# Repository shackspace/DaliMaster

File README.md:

DaliMaster
==========

A Dali master communication interface using custom circuit and openwrt on TP-Link MR-3020

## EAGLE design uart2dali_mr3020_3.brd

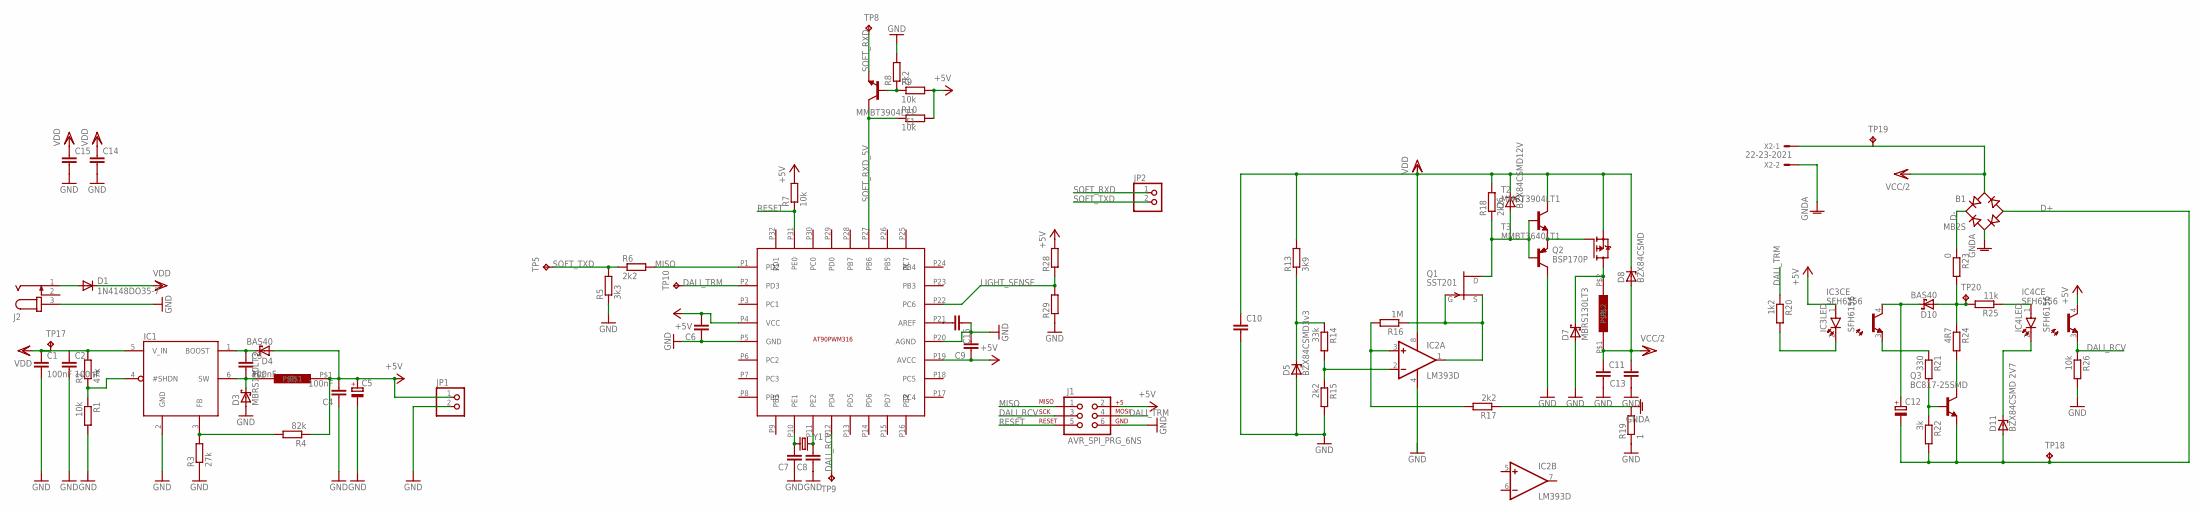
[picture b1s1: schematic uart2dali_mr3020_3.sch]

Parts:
B1: MB2S; SOIC-4
C1, C2, C3, C4: 100nF; C0805
C5: CPOL-EUCT7343; CT7343
C6, C7, C8, C9, C10, C16: C-EUC0603; C0603
C11, C13, C14, C15: C-EUC0805; C0805
C12: CPOL-EUCT6032; CT6032
D1: 1N4148DO35-7; DO35-7
D3, D7: MBRS130LT3; SMB
D4, D10: BAS40; SOT23
D5: BZX84CSMD3v3; TO236
D6: BZX84CSMD12V; TO236
D8: BZX84CSMD; TO236
D11: BZX84CSMD 2V7; TO236
IC1: LT1933ES6; SOT23-6
IC2: LM393D; SO08
IC3, IC4: SFH6156; SFH
J1: AVR_SPI_PRG_6NS; 2X3-NS
J2: JACK-PLUG1; SPC4078
JP1, JP2: PINHD-1X2; 1X02
Q1: SST201; SOT23
Q2: BSP170P; SOT223
Q3: BC817-25SMD; SOT23-BEC
R1, R7, R9, R10, R26: 10k; R0603
R2: 47k; R0603
R3: 27k; R0603
R4: 82k; R0603
R5: 3k3; R0603
R6, R8, R15, R17, R18: 2k2; R0603
R13: 3k9; R0603
R14: 33k; R0603
R16: 1M; R0603
R19: 1; R0603
R20: 1k2; R0603
R21: 330; R0603
R22: 3k; R0603
R23: 0; R0603
R24: 4R7; R0603
R25: 11k; R0603
R28: R-EU_0207/2V; 0207/2V
R29: R-EU_R0603; R0603
T1, T2: MMBT3904LT1; SOT23-BEC
T3: MMBT3640LT1; SOT23-BEC
TP5, TP8, TP9, TP10, TP17, TP18, TP19, TP20: TPB1,27; B1,27
U$1: KMP_2330_UNSHIELDED 33uH; KMP_2330_UNSHIELDED
U$2: AT90PWM316; QFN32_7MM
U$3: SDR0805
X2: 22-23-2021
Y1: CRYSTALTXC-7A; CRYSTAL-TXC-7A

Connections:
+5V: C4.2, C5.+, C6.2, C9.1, D4.1 (A), IC3.1 (A), IC4.4 (C), J1.2, JP1.1, R4.1, R7.2, R9.2, R10.2, R28.2, U$1.P$1, U$2.P4 (VCC), U$2.P19 (AVCC)
D+: B1.-, C12.-, D11.A, Q3.E, R22.2, TP18.TP
D-: B1.+, R23.1
DALI_RCV: J1.3, TP9.TP, U$2.P12 (PD4)
DALI_TRM: J1.4, R20.1, TP10.TP, U$2.P2 (PD3)
GND: C1.2, C2.2, C4.1, C5.-, C6.1, C7.1, C8.1, C9.2, C10.2, C11.2, C13.1, C14.2, C15.2, C16.1, D3.A, D5.A, D7.A, IC1.2 (GND), IC2.4 (V-), J1.6, J2.3, JP1.2, R1.2, R3.1, R5.1, R8.2, R15.2, R19.1, R26.2, R29.1, T3.C, U$2.P5 (GND), U$2.P20 (AGND)
GNDA: B1.~2 (AC2), R17.1, R19.2, X2.2
LIGHT_SENSE: R28.1, R29.2, U$2.P22 (PC6)
MISO: J1.1, R6.2, U$2.P1 (PD2)
unnamed: IC3.2 (K), R20.2
unnamed: IC2.2 (-IN), R14.2, R15.1
unnamed: IC1.4 (#SHDN), R1.1, R2.1
unnamed: C12.+, D10.3 (C), IC3.4 (C)
unnamed: IC3.3 (E), R21.1
unnamed: Q3.B, R21.2, R22.1
unnamed: IC4.3 (E), R26.1
unnamed: C16.2, U$2.P21 (AREF)
unnamed: D10.1 (A), R23.2, R24.1, R25.2, TP20.TP
unnamed: Q3.C, R24.2
unnamed: IC4.1 (A), R25.1
unnamed: D11.C, IC4.2 (K)
unnamed: C7.2, U$2.P10 (PE1), Y1.P$1 (1)
unnamed: C8.2, U$2.P11 (PE2), Y1.P$2 (2)
unnamed: R8.1, R9.1, T1.B
unnamed: IC2.1 (OUT), Q1.2 (S), Q1.3 (G), R16.1
unnamed: D1.A, J2.1
unnamed: C3.1, D4.3 (C), IC1.1 (BOOST)
unnamed: C3.2, D3.C, IC1.6 (SW), U$1.P$2
unnamed: D7.C, Q2.2 (D), Q2.4 (D), U$3.P$2
unnamed: IC1.3 (FB), R3.2, R4.2
unnamed: Q2.1 (G), T2.E, T3.E
unnamed: D6.A, Q1.1 (D), R18.1, T2.B, T3.B
unnamed: D5.C, R13.1, R14.1
unnamed: IC2.3 (+IN), R16.2, R17.2
RESET: J1.5, R7.1, U$2.P31 (PE0)
SOFT_RXD: JP2.1, T1.E, TP8.TP
SOFT_RXD_5V: R10.1, T1.C, U$2.P27 (PB6)
SOFT_TXD: JP2.2, R5.2, R6.1, TP5.TP
VCC/2: B1.~1 (AC1), C11.1, C13.2, D8.A, TP19.TP, U$3.P$1, X2.1
VDD: C1.1, C2.1, C10.1, C14.1, C15.1, D1.C, D6.C, D8.C, IC1.5 (V_IN), IC2.8 (V+), Q2.3 (S), R2.2, R13.2, R18.2, T2.C, TP17.TP

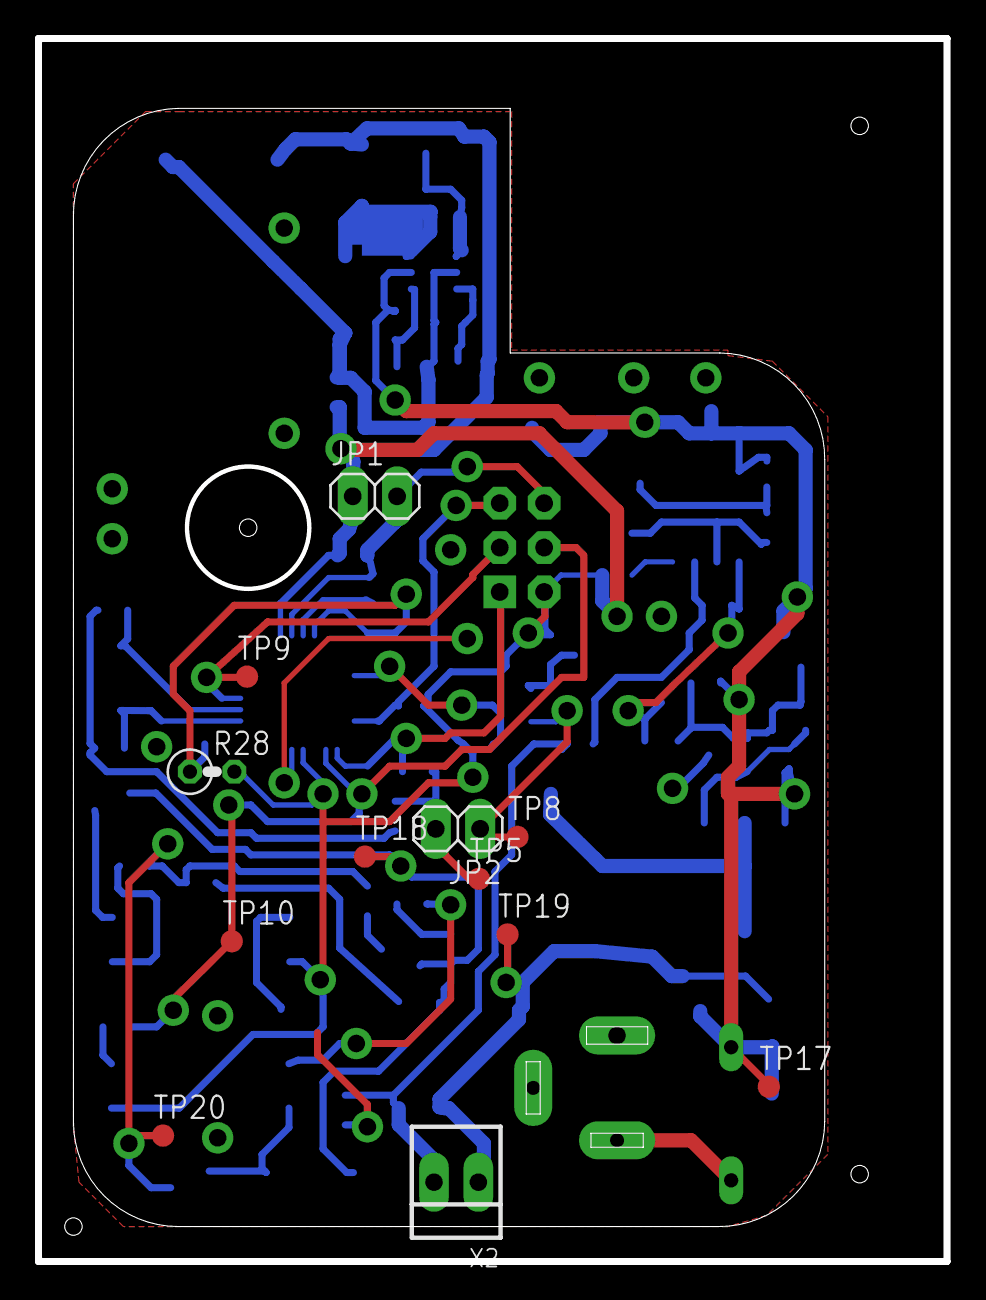
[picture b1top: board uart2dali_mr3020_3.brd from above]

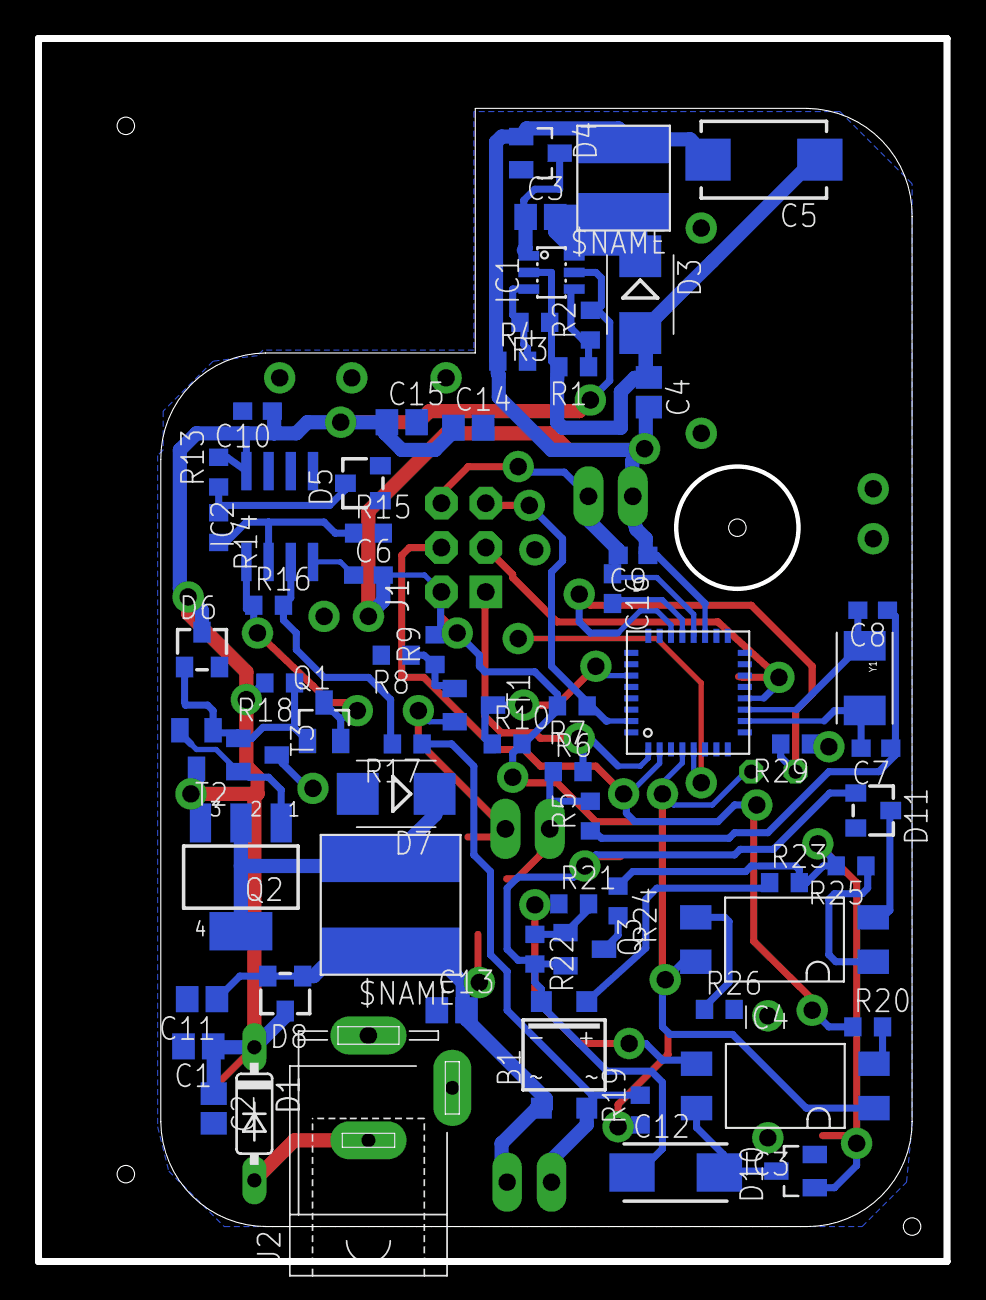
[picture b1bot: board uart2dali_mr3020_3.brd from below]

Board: 2 copper layers, 52.0 x 70.0 mm, 79 parts (67 on the bottom side), 40 nets.

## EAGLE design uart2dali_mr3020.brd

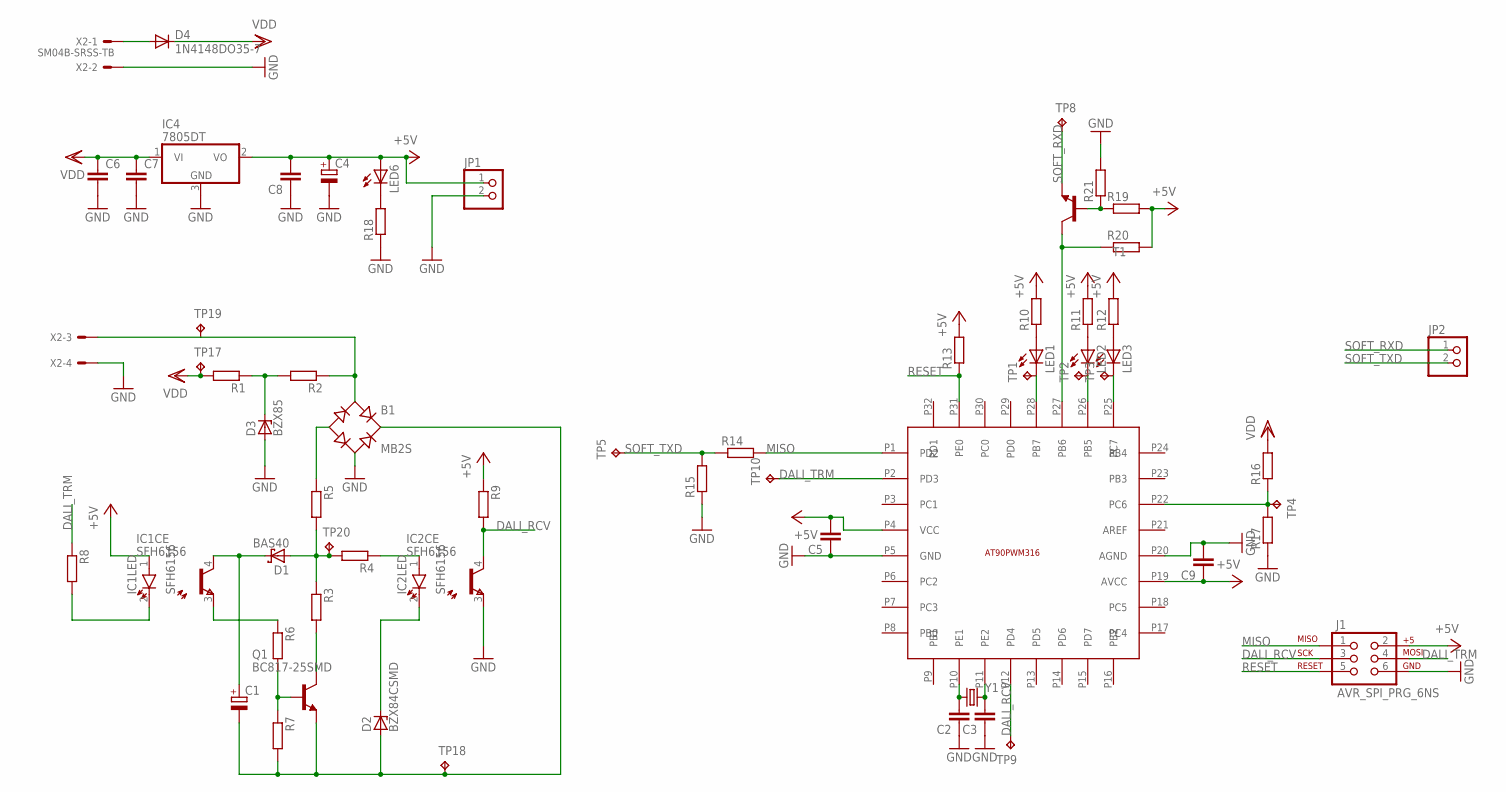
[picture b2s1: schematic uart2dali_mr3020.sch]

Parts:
B1: MB2S; SOIC-4
C1: CPOL-EUCT6032; CT6032
C2, C3, C5, C9: C-EUC0603; C0603
C4: CPOL-EUCT7343; CT7343
C6, C7, C8: C-EUC0805; C0805
D1: BAS40; SOT23
D2: BZX84CSMD; TO236
D3: BZX85; DO41Z10
D4: 1N4148DO35-7; DO35-7
IC1, IC2: SFH6156; SFH
IC4: 7805DT; TO252
J1: AVR_SPI_PRG_6NS; 2X3-NS
JP1, JP2: PINHD-1X2; 1X02
LED1, LED2, LED3, LED6: LEDCHIPLED_0805; CHIPLED_0805
Q1: BC817-25SMD; SOT23-BEC
R1, R2: R-EU_0204/7; 0204/7
R3, R4, R5, R6, R7, R8, R9, R10, R11, R12, R13, R14, R15, R16, R17, R18, R19, R20, R21: R-EU_R0603; R0603
T1: -NPN-SOT23-EBC; SOT23-EBC
TP1, TP2, TP3, TP4, TP5, TP8, TP9, TP10, TP17, TP18, TP19, TP20: TPB1,27; B1,27
U$1: AT90PWM316; QFN32_7MM
X2: SM04B-SRSS-TB
Y1: CRYSTALTXC-7A; CRYSTAL-TXC-7A

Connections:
+5V: C4.+, C5.2, C8.2, C9.1, IC1.1 (A), IC4.2 (VO), J1.2, JP1.1, LED6.A, R9.1, R10.2, R11.2, R12.2, R13.2, R19.2, R20.2, U$1.P4 (VCC), U$1.P19 (AVCC)
DALI_RCV: IC2.4 (C), J1.3, R9.2, TP9.TP, U$1.P12 (PD4)
DALI_TRM: J1.4, R8.1, TP10.TP, U$1.P2 (PD3)
GND: B1.~2 (AC2), C2.1, C3.1, C4.-, C5.1, C6.2, C7.2, C8.1, C9.2, D3.A, IC2.3 (E), IC4.3 (GND), J1.6, JP1.2, R15.1, R17.1, R18.1, R21.2, U$1.P5 (GND), U$1.P20 (AGND), X2.2, X2.4
MISO: J1.1, R14.2, U$1.P1 (PD2)
unnamed: IC1.2 (K), R8.2
unnamed: B1.~1 (AC1), R2.1, TP19.TP, X2.3
unnamed: D3.C, R1.1, R2.2
unnamed: C1.+, D1.3 (C), IC1.4 (C)
unnamed: IC1.3 (E), R6.1
unnamed: Q1.B, R6.2, R7.1
unnamed: B1.+, C1.-, D2.A, Q1.E, R7.2, TP18.TP
unnamed: LED1.A, R10.1
unnamed: D1.1 (A), R3.1, R4.2, R5.2, TP20.TP
unnamed: Q1.C, R3.2
unnamed: IC2.1 (A), R4.1
unnamed: D2.C, IC2.2 (K)
unnamed: B1.-, R5.1
unnamed: LED2.A, R11.1
unnamed: LED3.A, R12.1
unnamed: C2.2, U$1.P10 (PE1), Y1.P$1 (1)
unnamed: C3.2, U$1.P11 (PE2), Y1.P$2 (2)
unnamed: R19.1, R21.1, T1.B
unnamed: R20.1, T1.C, U$1.P27 (PB6)
unnamed: D4.A, X2.1
unnamed: LED3.C, TP3.TP, U$1.P25 (PC7)
unnamed: LED2.C, TP2.TP, U$1.P26 (PB5)
unnamed: LED1.C, TP1.TP, U$1.P28 (PB7)
unnamed: R16.1, R17.2, TP4.TP, U$1.P22 (PC6)
unnamed: LED6.C, R18.2
RESET: J1.5, R13.1, U$1.P31 (PE0)
SOFT_RXD: JP2.1, T1.E, TP8.TP
SOFT_TXD: JP2.2, R14.1, R15.2, TP5.TP
VDD: C6.1, C7.1, D4.C, IC4.1 (VI), R1.2, R16.2, TP17.TP

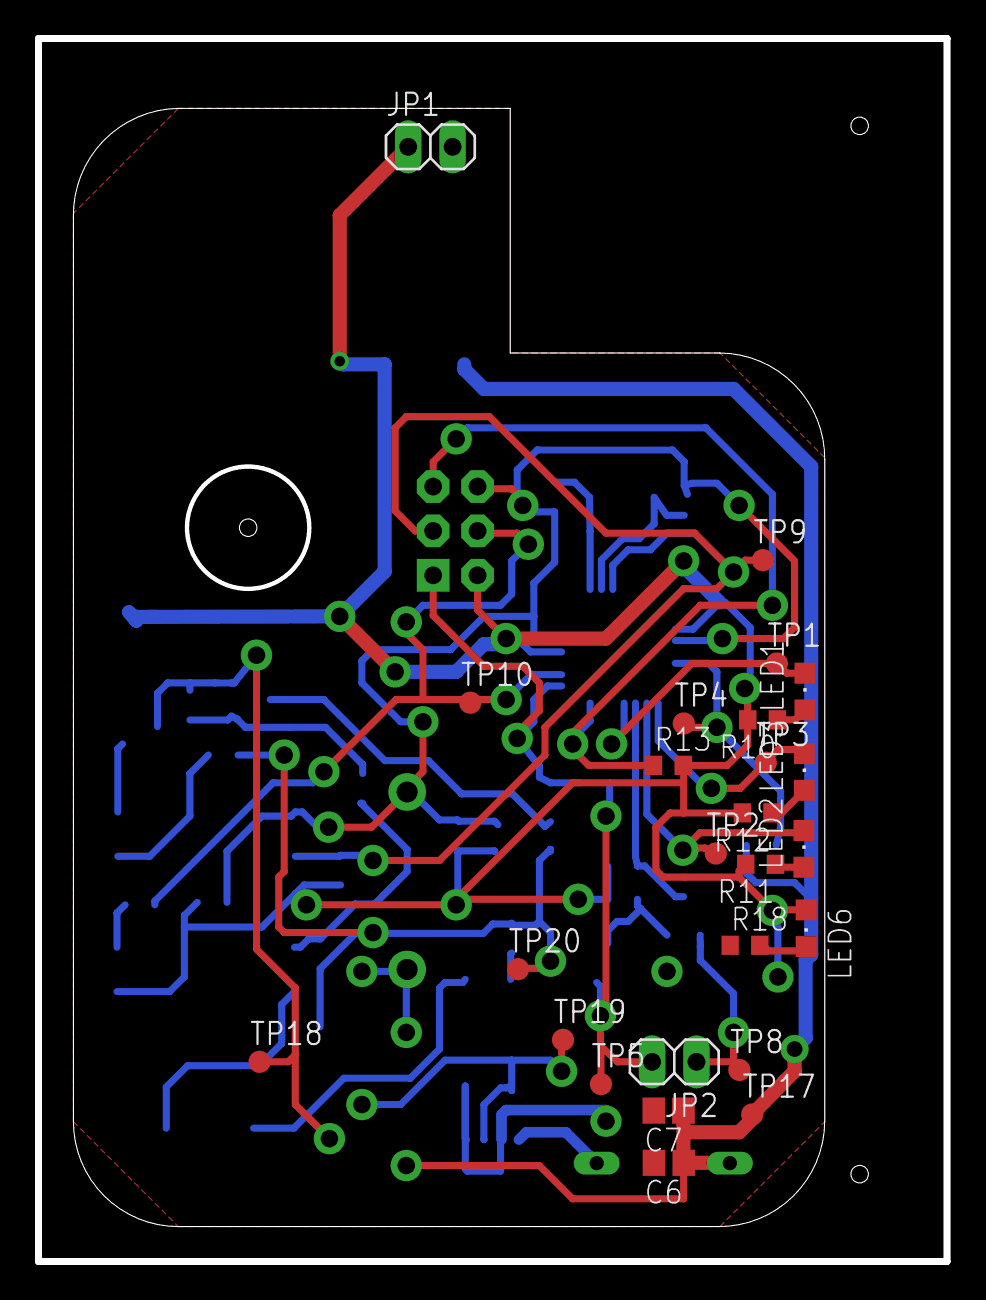
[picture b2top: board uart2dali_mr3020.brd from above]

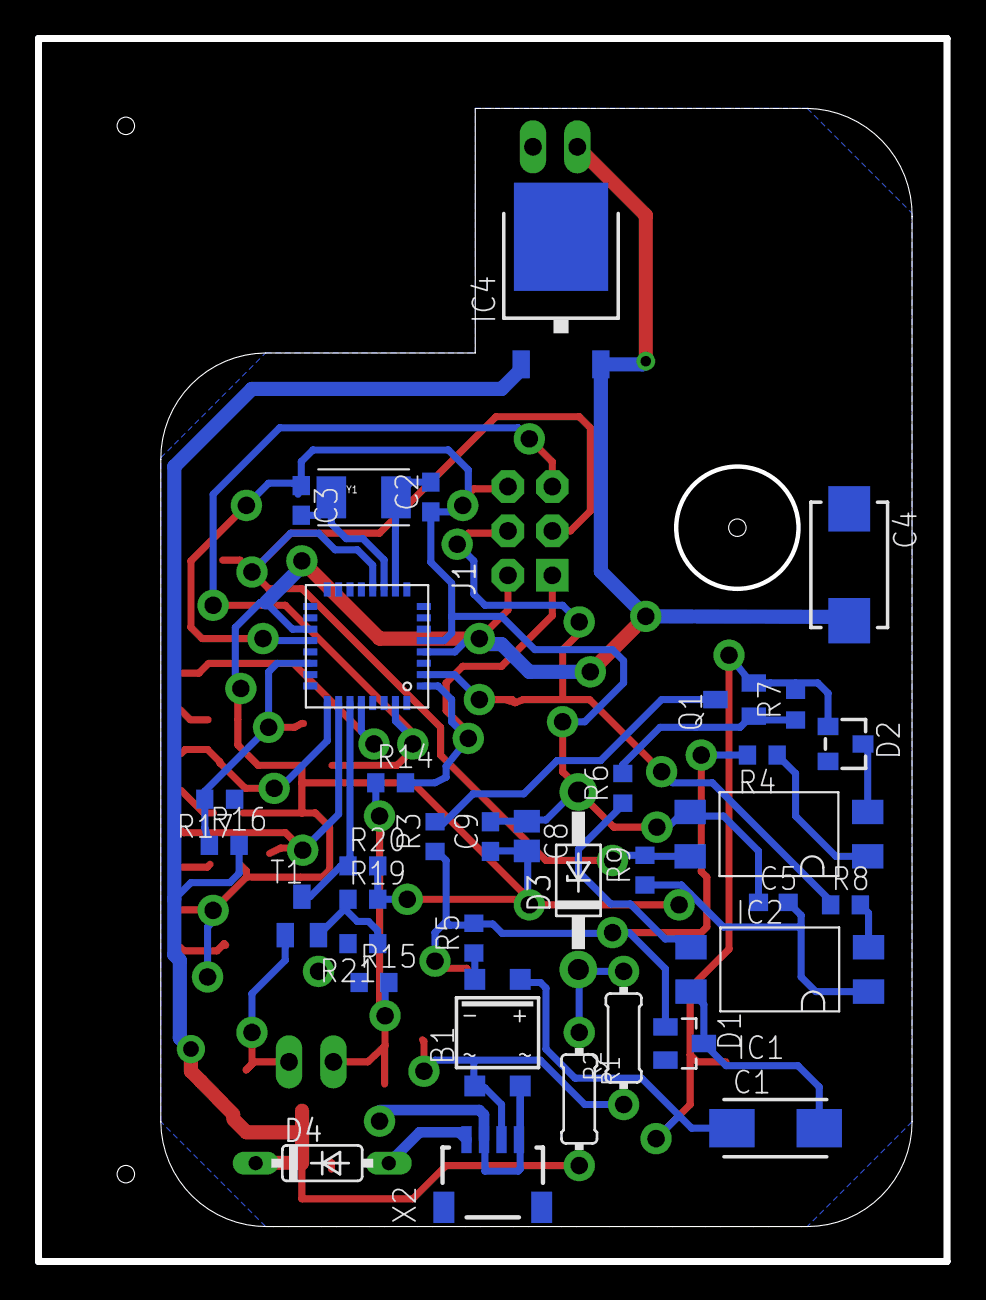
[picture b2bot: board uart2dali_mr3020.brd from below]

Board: 2 copper layers, 52.0 x 70.0 mm, 62 parts (37 on the bottom side), 34 nets.

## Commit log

2013-02-11 removed directories
2013-02-11 adding euart.c to scons file
2013-02-24 working on uart2dali board version 2 with switching voltage regulators
2013-03-10 new version of the base board with 2 switching regulators
2013-03-18 added encoder for dali codes
2013-03-18 - fixed mispelling in dali_encode - added dali_encode to SConstruct - minor fixes on schematics and board
2013-03-22 working on the message encoder
2013-03-22 misspelling
2013-03-23 introducing the interpreter
2013-03-24 adding command strings
2013-03-25 using a fifo (no overflow) for interpreter
2013-03-25 main routine written
2013-03-28 - added values parts of constant current circuit - dali master can query from slaves
2013-03-28 working on the interpreter
2013-03-28 Interpreter
2013-03-28 - preparing modules for module tests - working on interpreter
2013-03-28 found some bugs by debugging
2013-03-28 added firmware test
2013-03-29 found and fixed some bugs while unit testing
2013-03-29 tested up command for groups --> found a bug
2013-03-29 fixed bug while parsing direct level arc
2013-03-29 moar tests! using proper functions for getting strings from flash memory
2013-03-29 defined more commands
2013-03-29 added missing file
2013-03-29 implemented all commands
2013-03-29 adjusted count of commands
2013-03-29 added dali.h and dali.c to project
2013-03-30 found other bugs while testing
2013-03-30 some commands must be repeated
2013-03-31 new tests-cases
2013-04-01 Dali Master waits until router booted up
2013-04-05 found a bug in interpreter
2013-05-05 got dali master firmware to a "working" state
2013-07-19 - solved some warnings - changed optimizisation due compile problems - added startup_values which are send when controller is powered up. Start up values are saved in eeprom.
2013-07-19 new version of dali controler board
2013-10-07 - added some comments - fixes on layout
2014-03-02 - updated schematics and layout - some bugfixes in firmware
2014-03-02 added a list with possible parts from digikey
2021-02-25 Create LICENSE
    #1 add license

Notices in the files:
parts and their libraries:
SparkFun-FreqCtrl: Licensing: CC v3.0 Share-Alike You are welcome to use this library for commercial purposes.
